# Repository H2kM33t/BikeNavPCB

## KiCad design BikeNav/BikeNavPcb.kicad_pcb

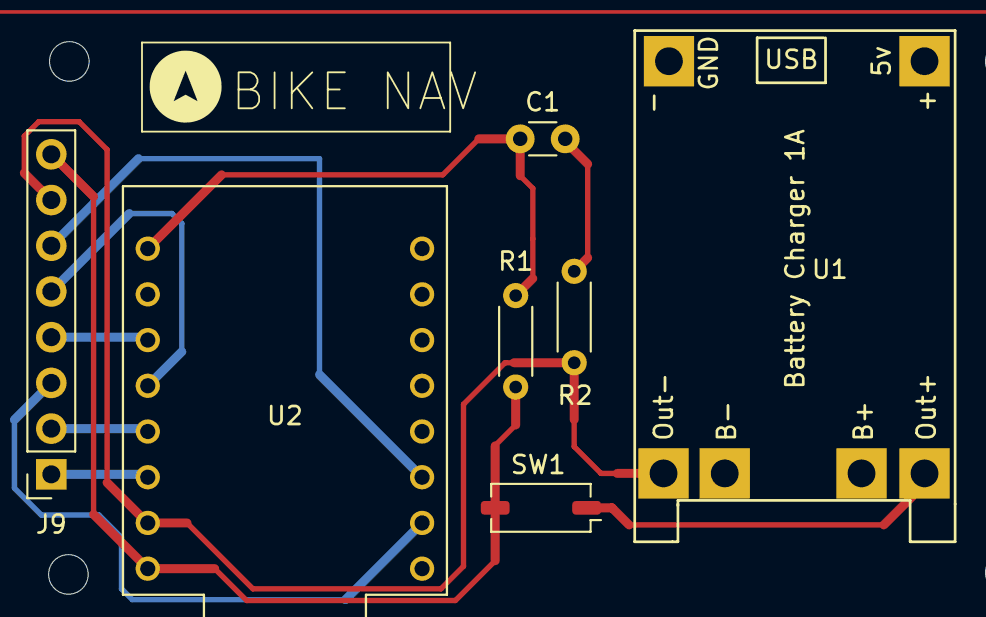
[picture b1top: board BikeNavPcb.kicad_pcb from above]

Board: 2 copper layers, 7 parts (0 on the bottom side), 11 nets.

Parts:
C1: 0.1 µF; C_Disc_D3.0mm_W1.6mm_P2.50mm
J9: 1.8 TFT SPi 128x160 pins; PinSocket_1x08_P2.54mm_Vertical
R1, R2: 100k; R_Axial_DIN0204_L3.6mm_D1.6mm_P5.08mm_Horizontal
SW1: SW_DPST_x2; SW_DIP_SPSTx01_Slide_Copal_CHS-01A_W5.08mm_P1.27mm_JPin
U1: TP4056
U2: ESP32-C3_SUPERMINI_TH; MODULE_ESP32-C3_SUPERMINI_TH

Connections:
/A0: J9.4, U2.2 (GPIO2)
/BACKLIGHT: J9.1, U2.3.3 (3V3)
/BATT EST: C1.1, R1.1, U2.0 (GPIO0)
/CS: J9.6, U2.7 (GPIO7)
/OUT+: J9.8, R1.2, SW1.2 (B), U2.5V
/OUT-: J9.7, R2.2, U1.4 (OUT-), U2.G (GND)
/RESET: J9.5, U2.3 (GPIO3)
/SCK: J9.2, U2.4 (GPIO4)
/SDA: J9.3, U2.6 (GPIO6)
unnamed: C1.2, R2.1
unnamed: SW1.1 (A), U1.3 (OUT+)
